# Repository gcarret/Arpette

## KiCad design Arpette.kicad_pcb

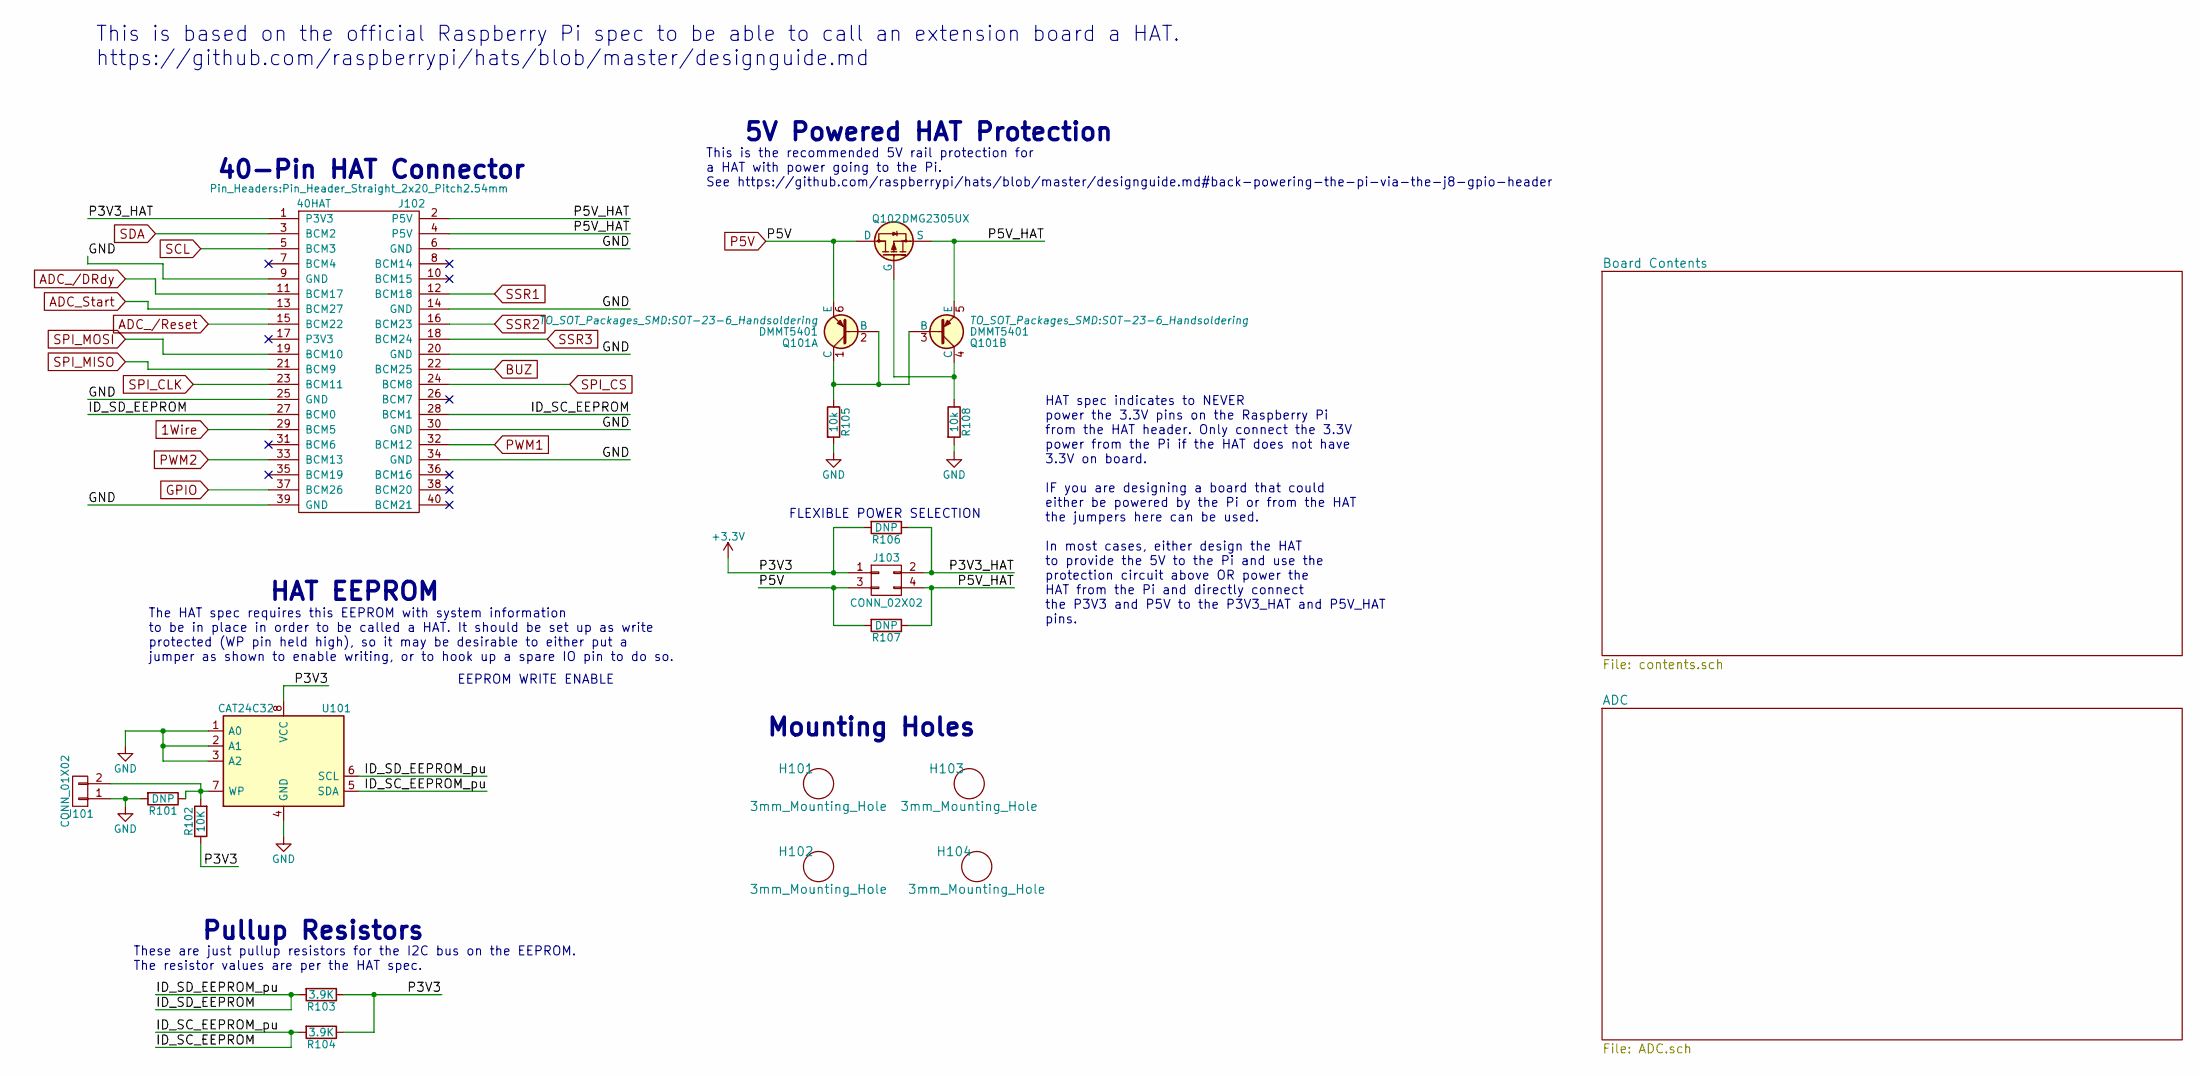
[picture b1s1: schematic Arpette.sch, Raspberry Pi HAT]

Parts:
H101, H102, H103, H104: 3mm_Mounting_Hole; NPTH_3mm_ID
J101: CONN_01X02; Pin_Header_Straight_1x02_Pitch1.27mm
J102: 40HAT; Pin_Header_Straight_2x20_Pitch2.54mm
J103: CONN_02X02; Pin_Header_Straight_2x02_Pitch1.27mm
Q101: DMMT5401; SOT-23-6_Handsoldering
Q102: DMG2305UX; SOT-23_Handsoldering
R101, R106, R107: DNP; R_0805_HandSoldering; MPN RC0402JR-0722RL
R102: 10K; R_0603_HandSoldering; MPN RC0402JR-0722RL
R103, R104: 3.9K; R_0603_HandSoldering; MPN RC0402JR-0722RL
R105, R108: 10k; R_0603_HandSoldering; MPN RC0402JR-0722RL
U101: CAT24C32; SOIC-8_3.9x4.9mm_Pitch1.27mm

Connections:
1Wire: J102.29 (BCM5); also elsewhere on the board
+3V3: J103.1, R102.1, R103.1, R104.1, R106.2, U101.8 (VCC); also elsewhere on the board
/ID_SC_EEPROM: J102.28 (BCM1), R104.2, U101.5 (SDA)
/ID_SD_EEPROM: J102.27 (BCM0), R103.2, U101.6 (SCL)
/P3V3_HAT: J102.1 (P3V3), J103.2, R106.1
/P5V_HAT: J102.2 (P5V), J102.4 (P5V), J103.4, Q101.5 (E), Q102.2 (S), R107.1
ADC_/DRdy: J102.11 (BCM17); also elsewhere on the board
ADC_/Reset: J102.15 (BCM22); also elsewhere on the board
ADC_Start: J102.13 (BCM27); also elsewhere on the board
BUZ: J102.22 (BCM25); also elsewhere on the board
GND: J101.1, J102.6 (GND), J102.9 (GND), J102.14 (GND), J102.20 (GND), J102.25 (GND), J102.30 (GND), J102.34 (GND), J102.39 (GND), R101.2, R105.2, R108.2, U101.1 (A0), U101.2 (A1), U101.3 (A2), U101.4 (GND); also elsewhere on the board
GPIO: J102.37 (BCM26); also elsewhere on the board
unnamed: J101.2, R101.1, R102.2, U101.7 (WP)
unnamed: Q101.1 (C), Q101.2 (B), Q101.3 (B), R105.1
unnamed: Q101.4 (C), Q102.1 (G), R108.1
P5V: J103.3, Q101.6 (E), Q102.3 (D), R107.2; also elsewhere on the board
PWM1: J102.32 (BCM12); also elsewhere on the board
PWM2: J102.33 (BCM13); also elsewhere on the board
SCL: J102.5 (BCM3); also elsewhere on the board
SDA: J102.3 (BCM2); also elsewhere on the board
SPI_CLK: J102.23 (BCM11); also elsewhere on the board
SPI_CS: J102.24 (BCM8); also elsewhere on the board
SPI_MISO: J102.21 (BCM9); also elsewhere on the board
SPI_MOSI: J102.19 (BCM10); also elsewhere on the board
SSR1: J102.12 (BCM18); also elsewhere on the board
SSR2: J102.16 (BCM23); also elsewhere on the board
SSR3: J102.18 (BCM24); also elsewhere on the board

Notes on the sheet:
FLEXIBLE POWER SELECTION
5V Powered HAT Protection
This is the recommended 5V rail protection for a HAT with power going to the Pi. See https://github.com/raspberrypi/hats/blob/master/designguide.md#back-powering-the-pi-via-the-j8-gpio-header
EEPROM WRITE ENABLE
Pullup Resistors
HAT EEPROM
Mounting Holes
40-Pin HAT Connector
HAT spec indicates to NEVER power the 3.3V pins on the Raspberry Pi from the HAT header. Only connect the 3.3V power from the Pi if the HAT does not have 3.3V on board. IF you are designing a board that could either be powered by the Pi or from the HAT the jumpers here can be used. In most cases, e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
The HAT spec requires this EEPROM with system information to be in place in order to be called a HAT. It should be set up as write protected (WP pin held high), so it may be desirable to either put a jumper as shown to enable writing, or to hook up a spare IO pin to do so.
These are just pullup resistors for the I2C bus on the EEPROM. The resistor values are per the HAT spec.
This is based on the official Raspberry Pi spec to be able to call an extension board a HAT. https://github.com/raspberrypi/hats/blob/master/designguide.md

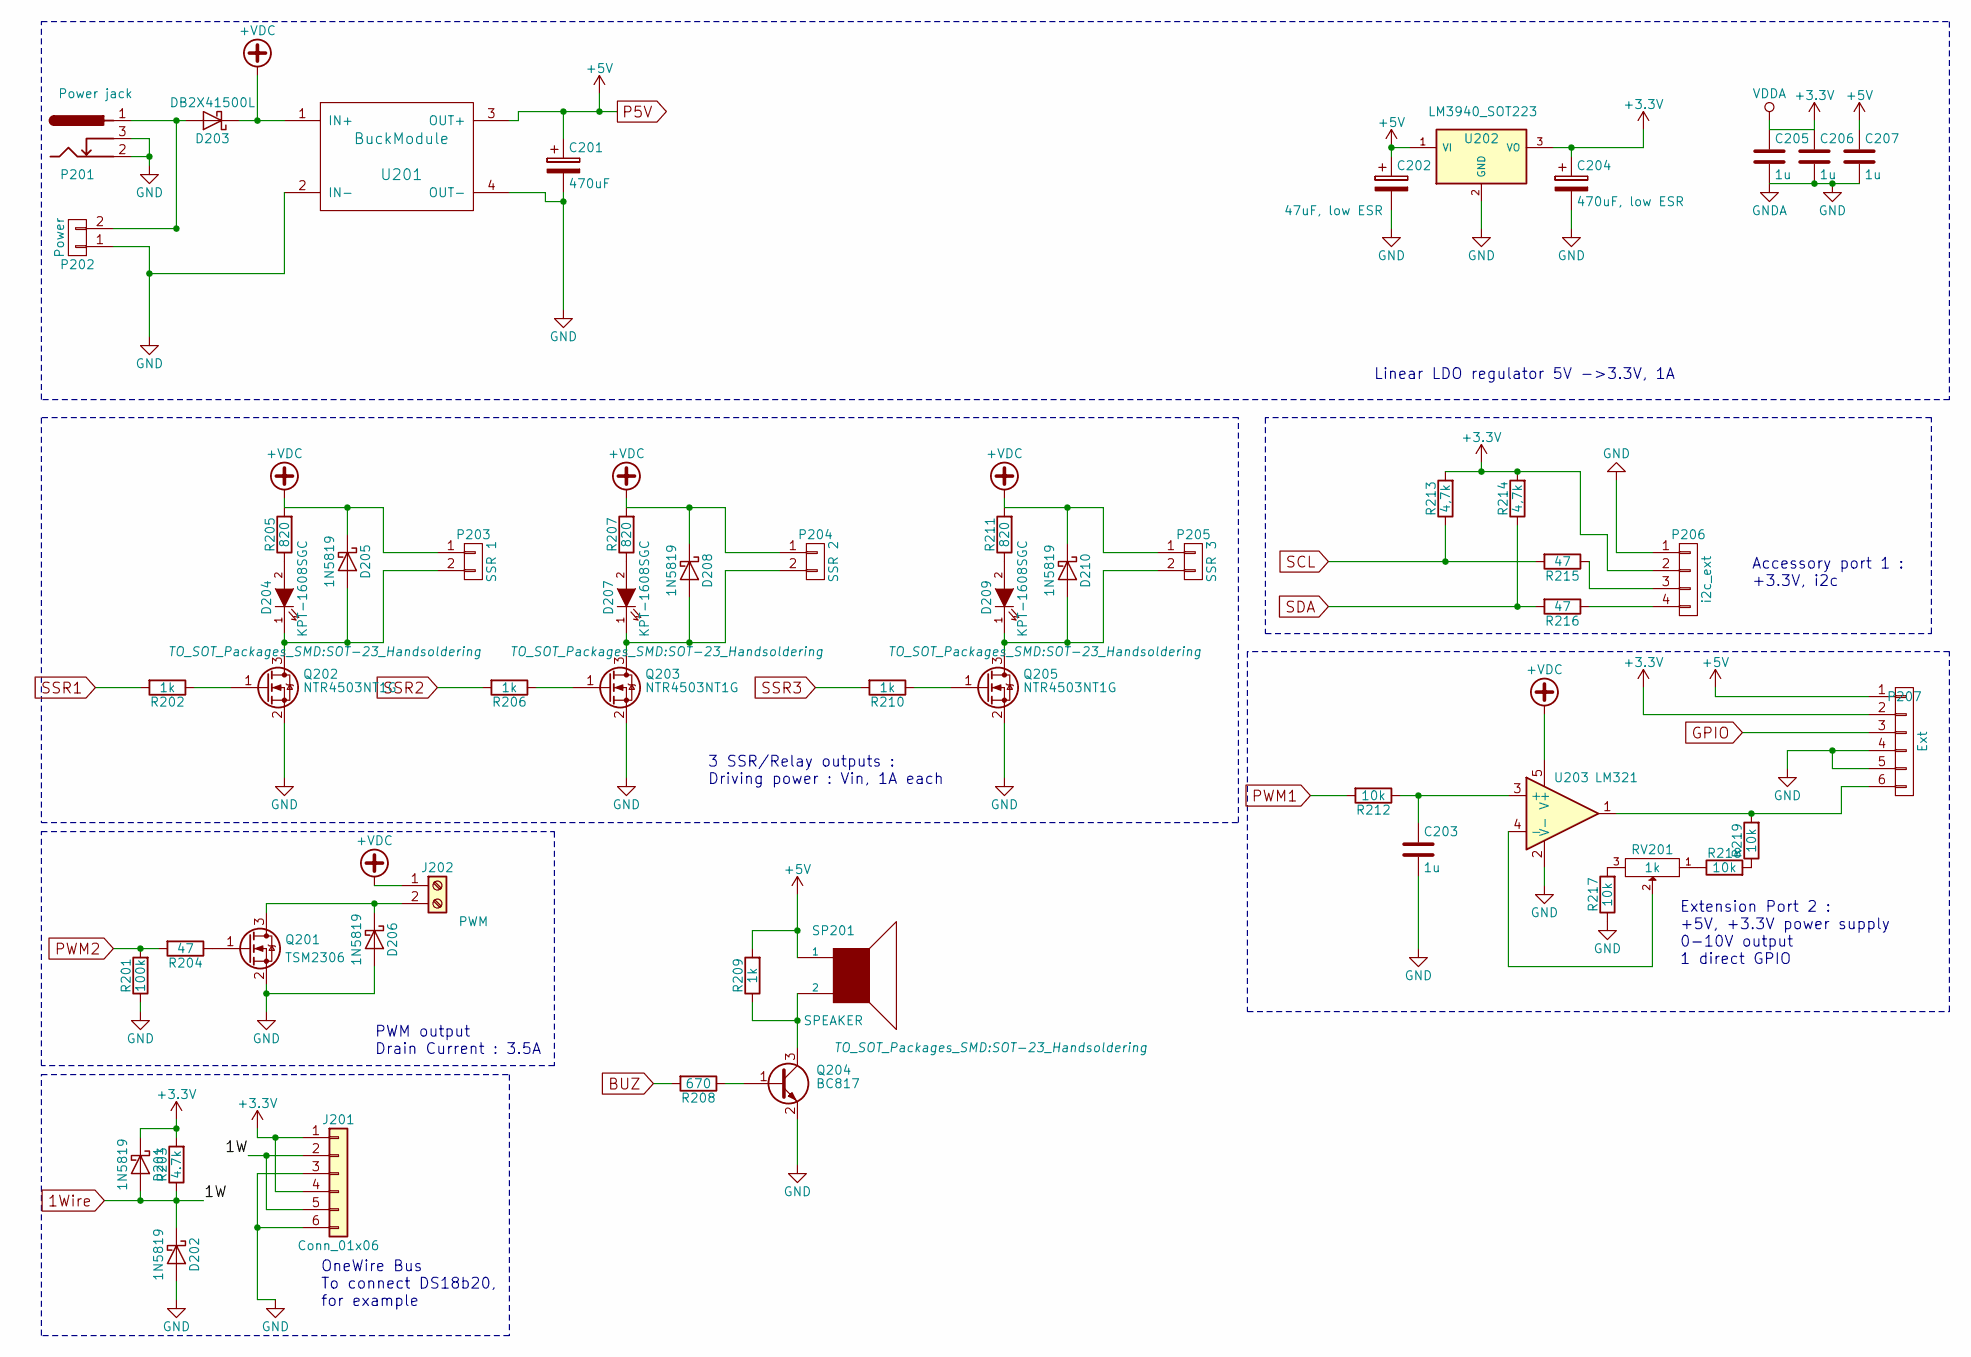
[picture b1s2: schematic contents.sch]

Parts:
C201: 470uF; CP_Elec_10x10.5
C202: 47uF, low ESR; CP_Elec_5x5.3
C203, C205, C206, C207: 1u; C_0805_HandSoldering
C204: 470uF, low ESR; CP_Elec_6.3x7.7
D201, D202, D205, D206, D208, D210: 1N5819; D_SOD-123
D203: DB2X41500L; D_SOD-123
D204, D207, D209: KPT-1608SGC; LED_0805_HandSoldering
J201: Conn_01x06; bornier6_2.54
J202: PWM; TerminalBlock_bornier-2_P5.08mm
P201: Power jack; BARREL_JACK
P202: Power; TerminalBlock_bornier-2_P5.08mm
P203: SSR 1; TerminalBlock_bornier-2_P5.08mm
P204: SSR 2; TerminalBlock_bornier-2_P5.08mm
P205: SSR 3; TerminalBlock_bornier-2_P5.08mm
P206: i2c_ext; Fan_Pin_Header_Straight_1x04
P207: Ext; PINHEAD1-6
Q201: TSM2306; SOT-23_Handsoldering
Q202, Q203, Q205: NTR4503NT1G; SOT-23_Handsoldering
Q204: BC817; SOT-23_Handsoldering
R201: 100k; R_0805_HandSoldering
R202, R206, R209, R210: 1k; R_0805_HandSoldering
R203: 4.7k; R_0805_HandSoldering
R204, R215, R216: 47; R_0805_HandSoldering
R205, R207, R211: 820; R_0805_HandSoldering
R208: 670; R_0805_HandSoldering
R212, R217, R218, R219: 10k; R_0805_HandSoldering
R213, R214: 4,7k; R_0805_HandSoldering
RV201: 1k; Potentiometer_Trimmer_Bourns_3266W
SP201: SPEAKER; CP_Radial_D12.5mm_P7.50mm
U201: BuckModule; Buck-Module-1
U202: LM3940_SOT223; SOT-223-3_TabPin2
U203: LM321; TSOT-23-5_HandSoldering

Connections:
1Wire: D201.2 (A), D202.1 (K), J201.2, J201.5, R203.1; also elsewhere on the board
+3V3: C204.1, C205.1, C206.1, D201.1 (K), J201.1, J201.4, P206.2, P207.2, R203.2, R213.2, R214.2, U202.3 (VO); also elsewhere on the board
+VDC: D203.1 (K), D205.1 (K), D208.1 (K), D210.1 (K), J202.1, P203.1, P204.1, P205.1, R205.2, R207.2, R211.2, U201.1 (IN+), U203.5 (V+)
BUZ: R208.2; also elsewhere on the board
GND: C201.2, C202.2, C203.2, C204.2, C205.2, C206.2, C207.2, D202.2 (A), D206.2 (A), J201.3, J201.6, P201.2, P201.3, P202.1, P206.1, P207.4, P207.5, Q201.2 (S), Q202.2 (S), Q203.2 (S), Q204.2 (E), Q205.2 (S), R201.1, R217.1, U201.2 (IN-), U201.4 (OUT-), U202.2 (GND), U203.2 (V-); also elsewhere on the board
GPIO: P207.3; also elsewhere on the board
unnamed: C203.1, R212.1, U203.3 (+)
unnamed: D203.2 (A), P201.1, P202.2
unnamed: D204.1 (K), D205.2 (A), P203.2, Q202.3 (D)
unnamed: D204.2 (A), R205.1
unnamed: D206.1 (K), J202.2, Q201.3 (D)
unnamed: D207.1 (K), D208.2 (A), P204.2, Q203.3 (D)
unnamed: D207.2 (A), R207.1
unnamed: D209.1 (K), D210.2 (A), P205.2, Q205.3 (D)
unnamed: D209.2 (A), R211.1
unnamed: P206.3, R215.1
unnamed: P206.4, R216.1
unnamed: P207.6, R219.2, U203.1
unnamed: Q201.1 (G), R204.1
unnamed: Q202.1 (G), R202.1
unnamed: Q203.1 (G), R206.1
unnamed: Q204.1 (B), R208.1
unnamed: Q204.3 (C), R209.1, SP201.2
unnamed: Q205.1 (G), R210.1
unnamed: R217.2, RV201.3
unnamed: R218.1, RV201.1
unnamed: R218.2, R219.1
unnamed: RV201.2, U203.4 (-)
P5V: C201.1, C202.1, C207.1, P207.1, R209.2, SP201.1, U201.3 (OUT+), U202.1 (VI); also elsewhere on the board
PWM1: R212.2; also elsewhere on the board
PWM2: R201.2, R204.2; also elsewhere on the board
SCL: R213.1, R215.2; also elsewhere on the board
SDA: R214.1, R216.2; also elsewhere on the board
SSR1: R202.2; also elsewhere on the board
SSR2: R206.2; also elsewhere on the board
SSR3: R210.2; also elsewhere on the board

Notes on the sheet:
Linear LDO regulator 5V ->3.3V, 1A
3 SSR/Relay outputs : Driving power : Vin, 1A each
Accessory port 1 : +3.3V, i2c
Extension Port 2 : +5V, +3.3V power supply 0-10V output 1 direct GPIO
PWM output Drain Current : 3.5A
OneWire Bus To connect DS18b20, for example

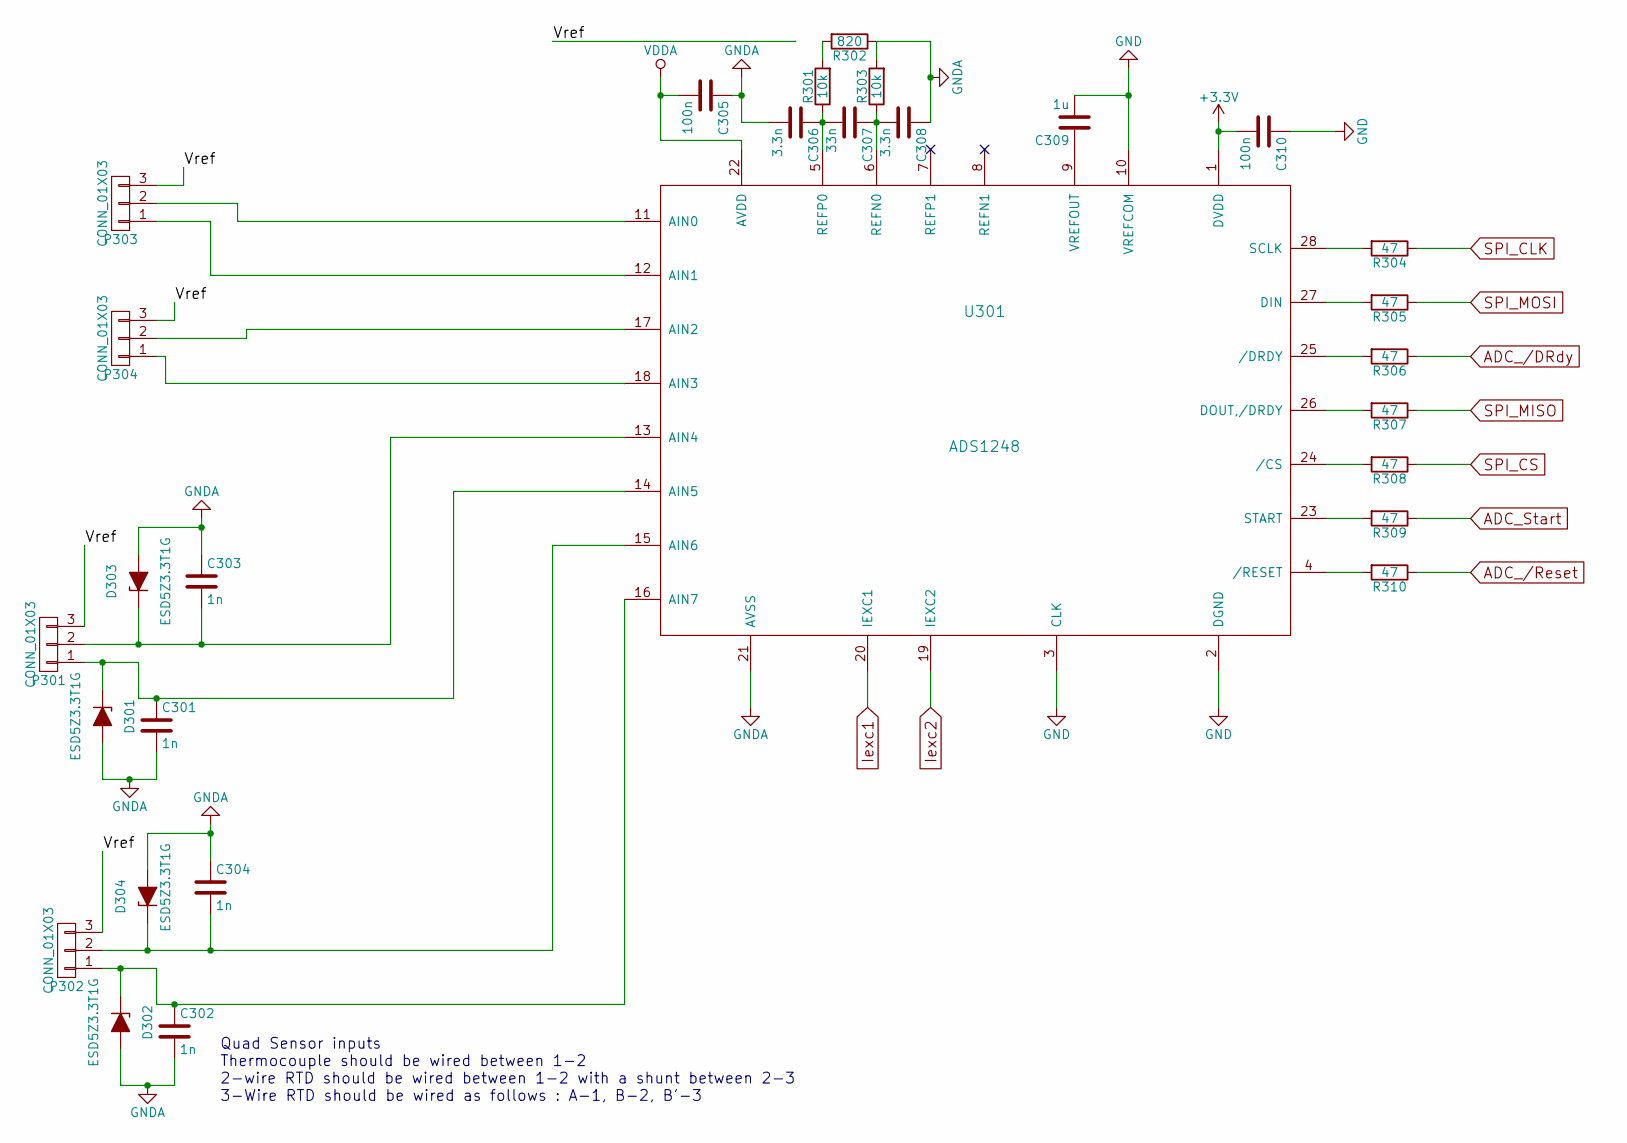
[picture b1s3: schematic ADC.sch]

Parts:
C301, C302, C303, C304: 1n; C_0805_HandSoldering
C305, C310: 100n; C_0805_HandSoldering
C306, C308: 3.3n; C_0805_HandSoldering
C307: 33n; C_0805_HandSoldering
C309: 1u; C_0805_HandSoldering
D301, D302, D303, D304: ESD5Z3.3T1G; D_SOD-523
P301, P302, P303, P304: CONN_01X03; Fan_Pin_Header_Straight_1x03
R301: 10k; R_0805_HandSoldering
R302: 820; R_0805_HandSoldering
R303: 10k; R_0603_HandSoldering
R304, R305, R306, R307, R308, R309, R310: 47; R_0603_HandSoldering
U301: ADS1248; TSSOP-28_4.4x9.7mm_Pitch0.65mm

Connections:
+3V3: C305.2, C310.2, U301.1 (DVDD), U301.22 (AVDD); also elsewhere on the board
/ADC/Vref: P301.3, P302.3, P303.3, P304.3
ADC_/DRdy: R306.1; also elsewhere on the board
ADC_/Reset: R310.1; also elsewhere on the board
ADC_Start: R309.1; also elsewhere on the board
GND: C301.2, C302.2, C303.1, C304.1, C305.1, C306.2, C308.1, C309.2, C310.1, D301.2 (A), D302.2 (A), D303.2 (A), D304.2 (A), R302.1, R303.2, U301.2 (DGND), U301.3 (CLK), U301.10 (VREFCOM), U301.21 (AVSS); also elsewhere on the board
unnamed: C301.1, D301.1 (K), P301.1, U301.14 (AIN5)
unnamed: C302.1, D302.1 (K), P302.1, U301.16 (AIN7)
unnamed: C303.2, D303.1 (K), P301.2, U301.13 (AIN4)
unnamed: C304.2, D304.1 (K), P302.2, U301.15 (AIN6)
unnamed: C306.1, C307.2, R301.1, U301.5 (REFP0)
unnamed: C307.1, C308.2, R303.1, U301.6 (REFN0)
unnamed: C309.1, U301.9 (VREFOUT)
unnamed: P303.1, U301.12 (AIN1)
unnamed: P303.2, U301.11 (AIN0)
unnamed: P304.1, U301.18 (AIN3)
unnamed: P304.2, U301.17 (AIN2)
unnamed: R301.2, R302.2
unnamed: R304.2, U301.28 (SCLK)
unnamed: R305.2, U301.27 (DIN)
unnamed: R306.2, U301.25 (/DRDY)
unnamed: R307.2, U301.26 (DOUT,/DRDY)
unnamed: R308.2, U301.24 (/CS)
unnamed: R309.2, U301.23 (START)
unnamed: R310.2, U301.4 (/RESET)
SPI_CLK: R304.1; also elsewhere on the board
SPI_CS: R308.1; also elsewhere on the board
SPI_MISO: R307.1; also elsewhere on the board
SPI_MOSI: R305.1; also elsewhere on the board

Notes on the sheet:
Quad Sensor inputs Thermocouple should be wired between 1-2 2-wire RTD should be wired between 1-2 with a shunt between 2-3 3-Wire RTD should be wired as follows : A-1, B-2, B'-3

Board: 2 copper layers, 102 parts (0 on the bottom side), 70 nets, no tracks yet.

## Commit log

2017-08-30 :boom::camel: Added .gitattributes & .gitignore files
2017-09-01 power
2017-09-05 Power supply
2017-09-12 Added multiple inputs
2017-09-13 Peripherals added
2017-09-13 component values
2017-09-14 ADC values
2017-09-18 PCB created
2017-12-19 Continued simplifiying
